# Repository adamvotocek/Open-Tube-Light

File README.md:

# Open-Tube-Light

An open-hardware LED tube fixture for stage and installation lighting. It takes Art-Net over Ethernet or DMX512 over XLR and drives a 144-pixel SK9822 strip inside an acrylic tube, with an OLED status display and buttons on the fixture.

## Repository layout

| Path | Contents |
|---|---|
| [`Code/Open-Tube-Light/`](Code/Open-Tube-Light/) | STM32H723 firmware (CubeMX + FreeRTOS + LwIP) — see its [README](Code/Open-Tube-Light/README.md) |
| [`PCB/ledTubeFixture/`](PCB/ledTubeFixture/) | Main board, KiCad (MCU, Ethernet, DMX, power, display & buttons) |
| [`PCB/xlrConBoards/`](PCB/xlrConBoards/) | XLR connector boards, KiCad |
| [`PCB/releases/`](PCB/releases/) | Fabrication packages for released board revisions |
| [`PCB/TODOs.txt`](PCB/TODOs.txt) | Known issues for the next board revision |
| [`Enclosure/`](Enclosure/) | Mechanical drawings (acrylic tube) |

## Art-Net

The fixture is an Art-Net 4 node (output only). Discovery (ArtPoll), ArtSync, ArtCommand and ArtDataRequest (product, user guide and support URLs) are supported. Spec coverage is tracked in [`Code/Open-Tube-Light/docs/artnet-compliance.md`](Code/Open-Tube-Light/docs/artnet-compliance.md).

**Multiple controllers / merging.** The fixture does not merge (no HTP/LTP). Each universe is owned by the first controller that sends ArtDmx to it. ArtDmx for that universe from any other IP address is ignored until the owner has sent nothing for 5 seconds, after which the next sender takes over. ArtSync is honoured per controller: a universe enters synchronous mode only on ArtSync from its own controller.

Art-Net™ Designed by and Copyright Artistic Licence

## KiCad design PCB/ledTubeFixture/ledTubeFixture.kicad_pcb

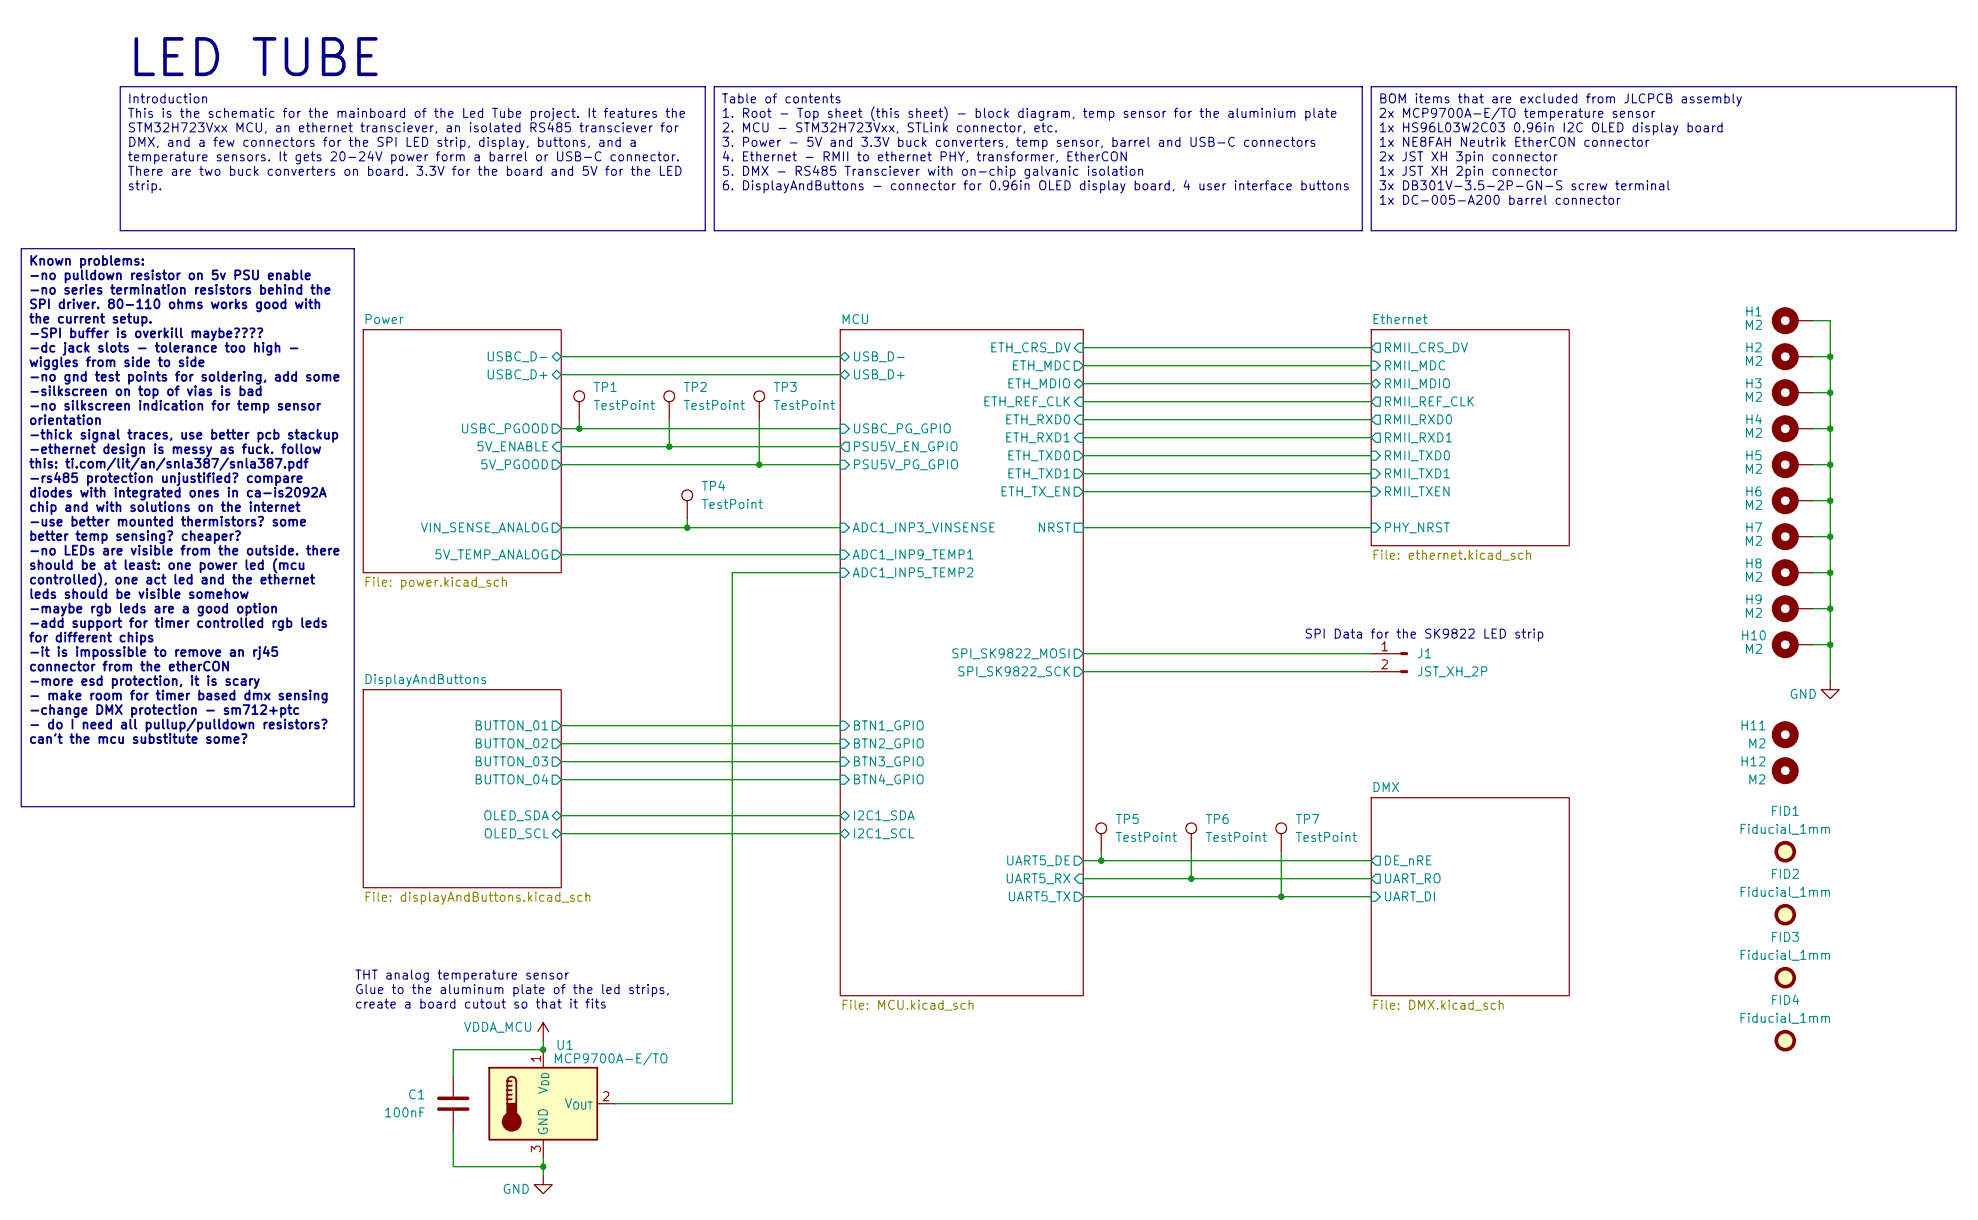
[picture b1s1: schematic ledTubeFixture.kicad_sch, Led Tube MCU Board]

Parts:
C1: 100nF; C_0402_1005Metric; LCSC C1525
FID1, FID2, FID3, FID4: Fiducial_1mm; Fiducial_1mm_Mask2mm
H1, H2, H3, H4, H5, H6, H7, H8, H9, H10: M2; MountingHole_2.2mm_M2_Pad_Via
H11, H12: M2; MountingHole_2.2mm_M2
J1: JST_XH_2P; JST_XH_B2B-XH-A_1x02_P2.50mm_Vertical
TP1, TP2, TP3, TP4, TP5, TP6, TP7: TestPoint; TestPoint_Pad_D1.0mm
U1: MCP9700A-E/TO; TO-92_Inline

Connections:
/DMX/DE_nRE: TP5.1; also elsewhere on the board
/DMX/UART_DI: TP7.1; also elsewhere on the board
/DMX/UART_RO: TP6.1; also elsewhere on the board
/MCU/ADC1_INP3_VINSENSE: TP4.1; also elsewhere on the board
/MCU/ADC1_INP5_TEMP2: U1.2 (V_{OUT}); also elsewhere on the board
/MCU/PSU5V_PG_GPIO: TP3.1; also elsewhere on the board
/MCU/SPI_SK9822_MOSI: J1.1; also elsewhere on the board
/MCU/SPI_SK9822_SCK: J1.2; also elsewhere on the board
/MCU/USBC_PG_GPIO: TP1.1; also elsewhere on the board
/Power/5V_ENABLE: TP2.1; also elsewhere on the board
GND: C1.2, H1.1, H2.1, H3.1, H4.1, H5.1, H6.1, H7.1, H8.1, H9.1, H10.1, U1.3 (GND); also elsewhere on the board
VDDA_MCU: C1.1, U1.1 (V_{DD}); also elsewhere on the board

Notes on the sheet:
THT analog temperature sensor Glue to the aluminum plate of the led strips, create a board cutout so that it fits
LED TUBE
SPI Data for the SK9822 LED strip
Known problems: -no pulldown resistor on 5v PSU enable -no series termination resistors behind the SPI driver. 80-110 ohms works good with the current setup. -SPI buffer is overkill maybe???? -dc jack slots - tolerance too high - wiggles from side to side -no gnd test points for soldering, add some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
Introduction This is the schematic for the mainboard of the Led Tube project. It features the STM32H723Vxx MCU, an ethernet transciever, an isolated RS485 transciever for DMX, and a few connectors for the SPI LED strip, display, buttons, and a temperature sensors. It gets 20-24V power form a barrel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
BOM items that are excluded from JLCPCB assembly 2x MCP9700A-E/TO temperature sensor 1x HS96L03W2C03 0.96in I2C OLED display board 1x NE8FAH Neutrik EtherCON connector 2x JST XH 3pin connector 1x JST XH 2pin connector 3x DB301V-3.5-2P-GN-S screw terminal 1x DC-005-A200 barrel connector
Table of contents 1. Root - Top sheet (this sheet) - block diagram, temp sensor for the aluminium plate 2. MCU - STM32H723Vxx, STLink connector, etc. 3. Power - 5V and 3.3V buck converters, temp sensor, barrel and USB-C connectors 4. Ethernet - RMII to ethernet PHY, transformer, EtherCON 5. DMX - R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

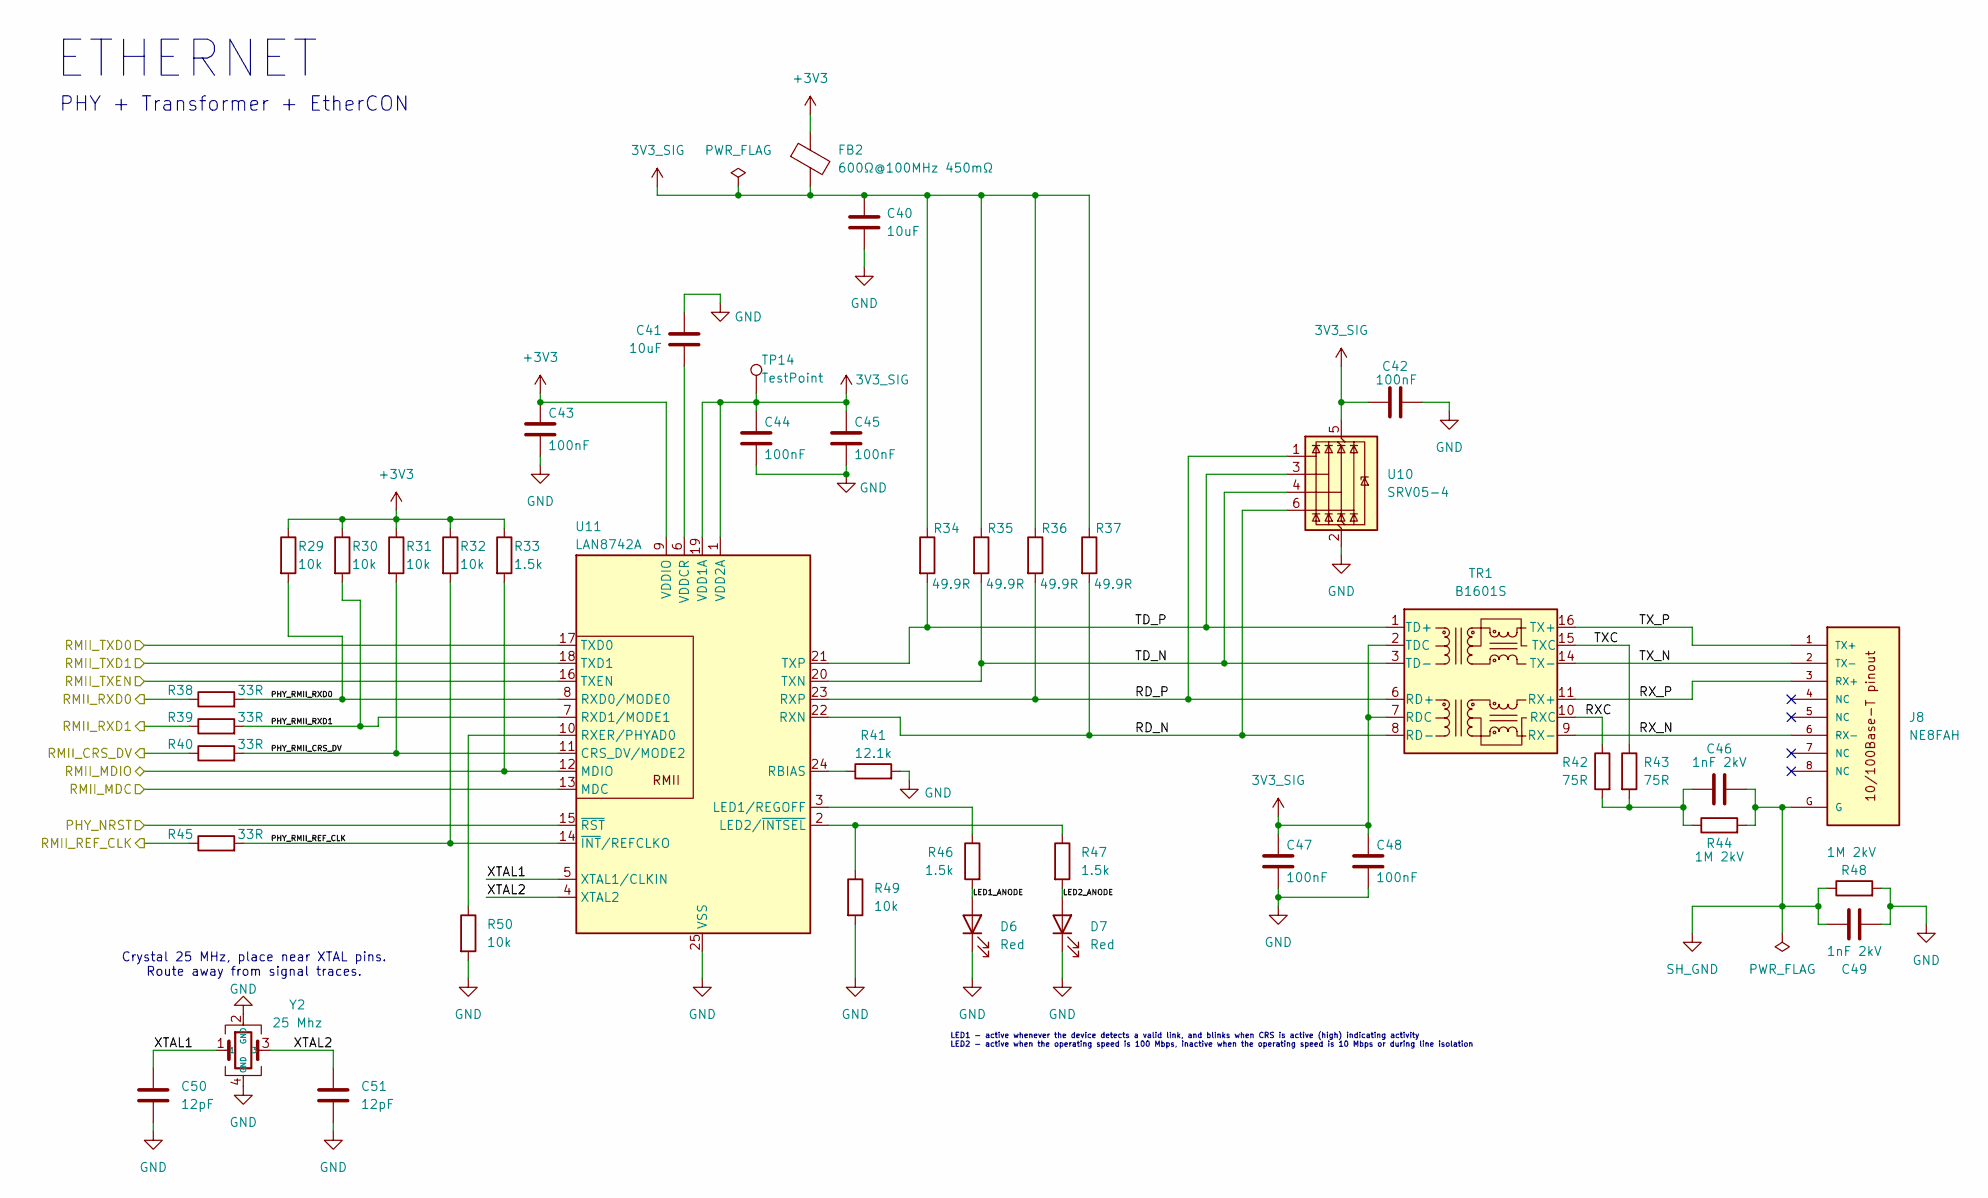
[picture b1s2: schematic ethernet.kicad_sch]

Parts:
C40, C41: 10uF; C_0603_1608Metric; LCSC C19702
C42, C43, C44, C45, C47, C48: 100nF; C_0402_1005Metric; LCSC C1525
C46, C49: 1nF 2kV; C_1206_3216Metric; LCSC C9196
C50, C51: 12pF; C_0402_1005Metric; LCSC C1547
D6, D7: Red; LED_0603_1608Metric; LCSC C2286
FB2: 600Ω@100MHz 450mΩ; C_0603_1608Metric; LCSC C1002
J8: NE8FAH; NEUTRIK_NE8FAH; PARTREV 16.04.02; LCSC C368497
R29, R30, R31, R32, R49, R50: 10k; R_0402_1005Metric; LCSC C25744
R33, R46, R47: 1.5k; R_0402_1005Metric; LCSC C25867
R34, R35, R36, R37: 49.9R; R_0402_1005Metric; LCSC C25120
R38, R39, R40, R45: 33R; R_0402_1005Metric; LCSC C25105
R41: 12.1k; R_0402_1005Metric; LCSC C2933069
R42, R43: 75R; R_0603_1608Metric; LCSC C4275
R44, R48: 1M 2kV; R_2010_5025Metric; LCSC C2779367
TP14: TestPoint; TestPoint_Pad_D1.0mm
TR1: B1601S; Transformer_Ethernet_B1601S; LCSC C510548
U10: SRV05-4; SOT-23-6; LCSC C7420376
U11: LAN8742A; LAN8742A_VQFN-24-1EP_4x4mm_P0.5mm_EP2.5x2.5mm; LCSC C621425
Y2: 25 Mhz; Crystal_SMD_3225-4Pin_3.2x2.5mm; LCSC C9006

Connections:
3V3_SIG: C40.1, C42.1, C44.1, C45.1, C47.1, C48.1, FB2.2, R34.1, R35.1, R36.1, R37.1, TP14.1, TR1.2 (TDC), TR1.7 (RDC), U10.5 (VBUS), U11.1 (VDD2A), U11.19 (VDD1A)
+3V3: C43.1, FB2.1, R29.1, R30.1, R31.1, R32.1, R33.1, U11.9 (VDDIO); also elsewhere on the board
/Ethernet/LED1_ANODE: D6.2 (A), R46.2
/Ethernet/LED2_ANODE: D7.2 (A), R47.2
/Ethernet/PHY_RMII_CRS_DV: R31.2, R40.2, U11.11 (CRS_DV/MODE2)
/Ethernet/PHY_RMII_REF_CLK: R32.2, R45.2, U11.14 (~INT/REFCLKO)
/Ethernet/PHY_RMII_RXD0: R29.2, R38.2, U11.8 (RXD0/MODE0)
/Ethernet/PHY_RMII_RXD1: R30.2, R39.2, U11.7 (RXD1/MODE1)
/Ethernet/RD_N: R37.2, TR1.8 (RD-), U10.6 (I/O4), U11.22 (RXN)
/Ethernet/RD_P: R36.2, TR1.6 (RD+), U10.1 (I/O1), U11.23 (RXP)
/Ethernet/RMII_CRS_DV: R40.1; also elsewhere on the board
/Ethernet/RMII_MDC: U11.13 (MDC); also elsewhere on the board
/Ethernet/RMII_MDIO: R33.2, U11.12 (MDIO); also elsewhere on the board
/Ethernet/RMII_REF_CLK: R45.1; also elsewhere on the board
/Ethernet/RMII_RXD0: R38.1; also elsewhere on the board
/Ethernet/RMII_RXD1: R39.1; also elsewhere on the board
/Ethernet/RMII_TXD0: U11.17 (TXD0); also elsewhere on the board
/Ethernet/RMII_TXD1: U11.18 (TXD1); also elsewhere on the board
/Ethernet/RMII_TXEN: U11.16 (TXEN); also elsewhere on the board
/Ethernet/RXC: R42.1, TR1.10 (RXC)
/Ethernet/RX_N: J8.6 (RX-), TR1.9 (RX-)
/Ethernet/RX_P: J8.3 (RX+), TR1.11 (RX+)
/Ethernet/TD_N: R35.2, TR1.3 (TD-), U10.4 (I/O3), U11.20 (TXN)
/Ethernet/TD_P: R34.2, TR1.1 (TD+), U10.3 (I/O2), U11.21 (TXP)
/Ethernet/TXC: R43.1, TR1.15 (TXC)
/Ethernet/TX_N: J8.2 (TX-), TR1.14 (TX-)
/Ethernet/TX_P: J8.1 (TX+), TR1.16 (TX+)
/Ethernet/XTAL1: C50.1, U11.5 (XTAL1/CLKIN), Y2.1
/Ethernet/XTAL2: C51.1, U11.4 (XTAL2), Y2.3
/MCU/NRST: U11.15 (~RST); also elsewhere on the board
GND: C40.2, C41.1, C42.2, C43.2, C44.2, C45.2, C47.2, C48.2, C49.1, C50.2, C51.2, D6.1 (K), D7.1 (K), R41.2, R48.2, R49.2, R50.2, U10.2 (GND), U11.25 (VSS), Y2.2 (GND), Y2.4 (GND); also elsewhere on the board
unnamed: C46.1, R42.2, R43.2, R44.1
unnamed: R46.1, U11.3 (LED1/REGOFF)
unnamed: R47.1, R49.1, U11.2 (LED2/~INTSEL)
unnamed: R41.1, U11.24 (RBIAS)
unnamed: R50.1, U11.10 (RXER/PHYAD0)
unnamed: C41.2, U11.6 (VDDCR)
SH_GND: C46.2, C49.2, J8.G, R44.2, R48.1

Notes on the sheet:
LED1 - active whenever the device detects a valid link, and blinks when CRS is active (high) indicating activity LED2 - active when the operating speed is 100 Mbps, inactive when the operating speed is 10 Mbps or during line isolation
PHY + Transformer + EtherCON
ETHERNET
Crystal 25 MHz, place near XTAL pins. Route away from signal traces.

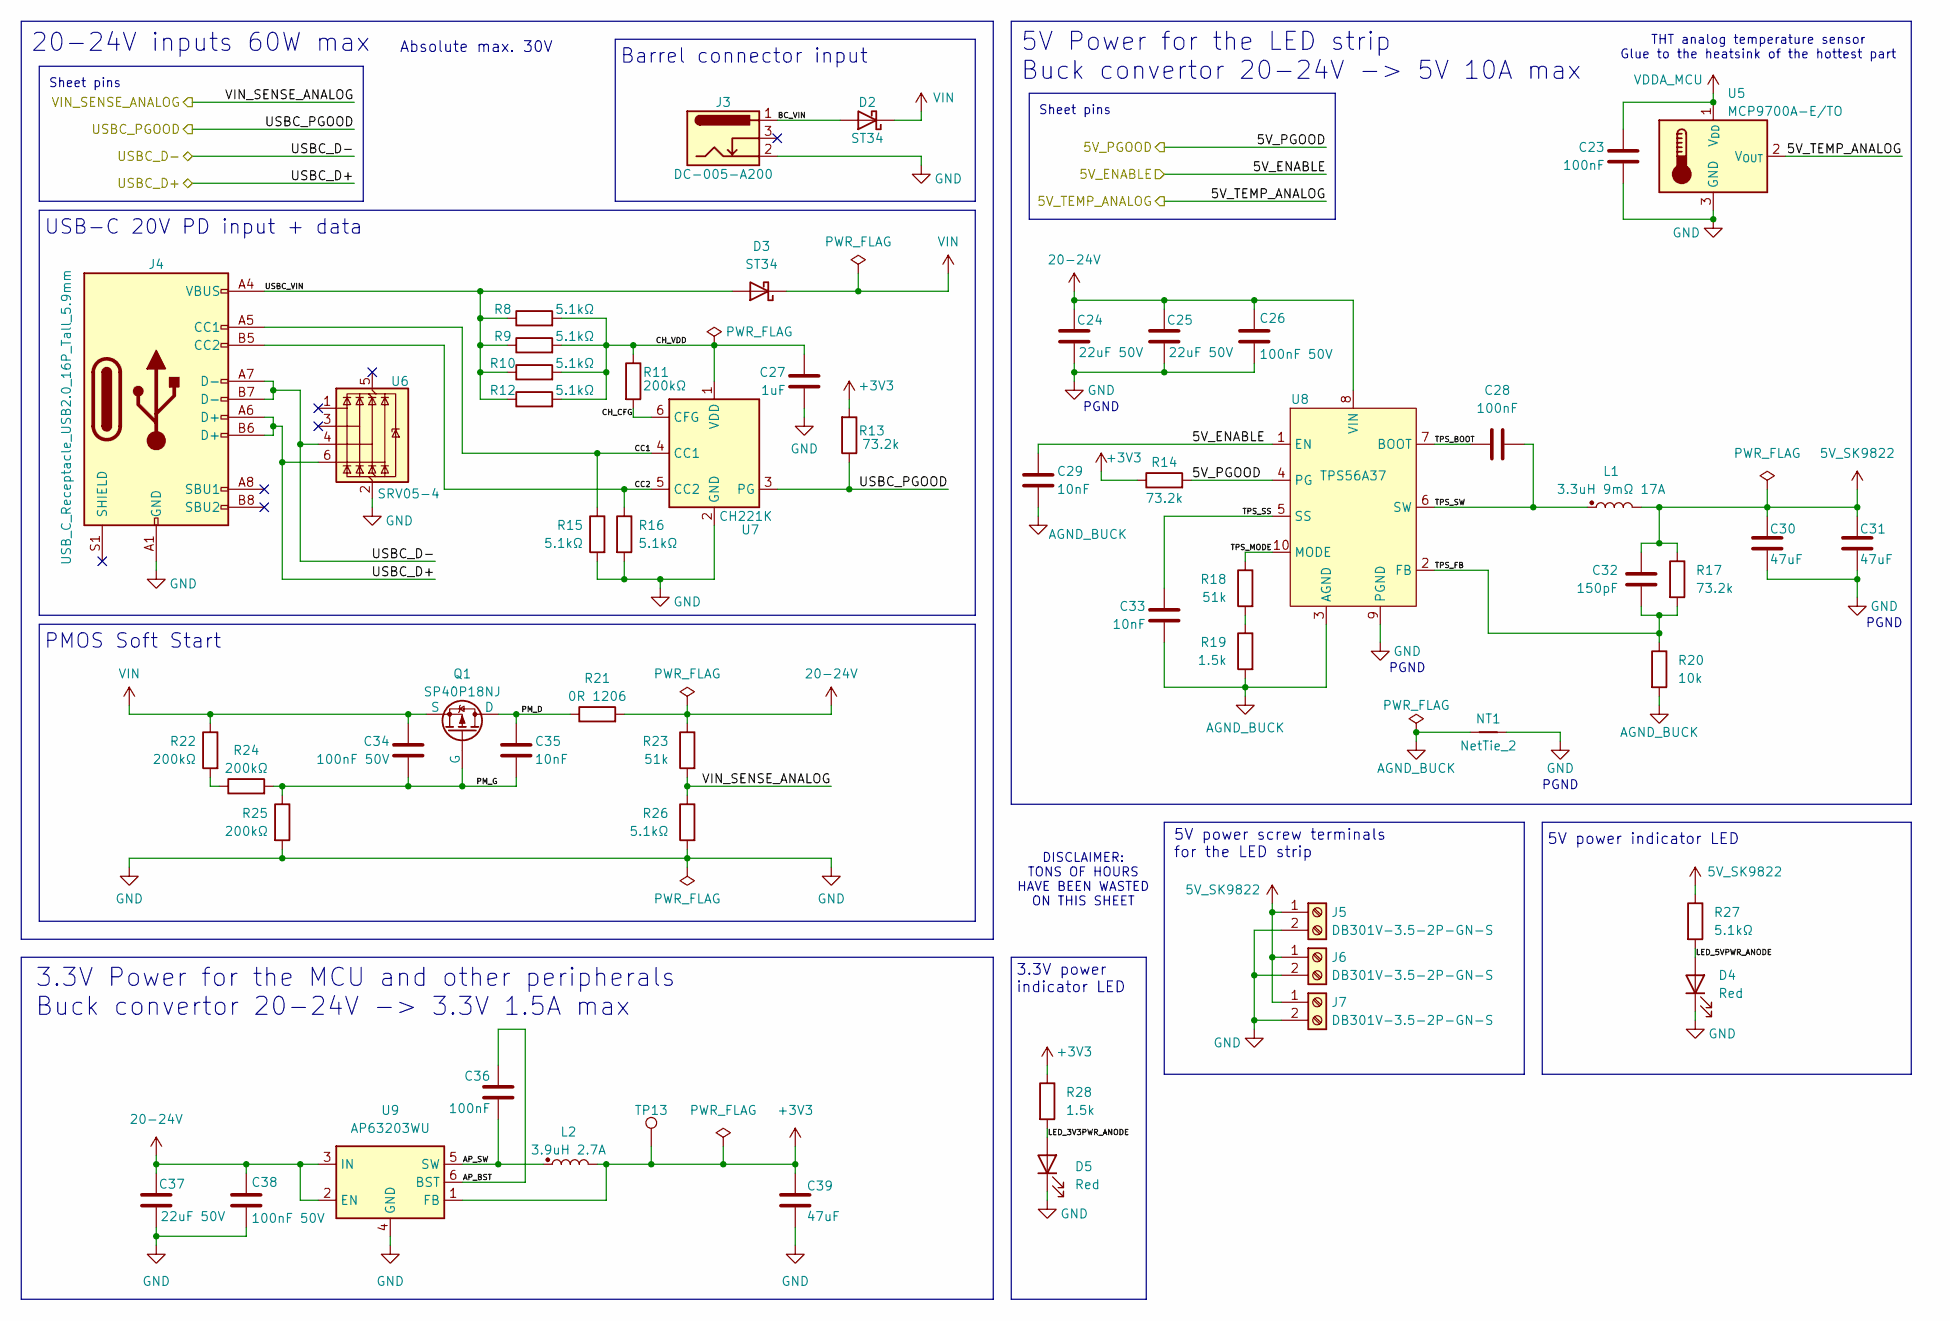
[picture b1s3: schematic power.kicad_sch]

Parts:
C23, C28, C36: 100nF; C_0402_1005Metric; LCSC C1525
C24, C25, C37: 22uF 50V; C_1812_4532Metric; LCSC C22388553
C26, C34, C38: 100nF 50V; C_0402_1005Metric; LCSC C307331
C27: 1uF; C_0402_1005Metric; LCSC C52923
C29, C33, C35: 10nF; C_0402_1005Metric; LCSC C15195
C30, C31, C39: 47uF; C_1210_3225Metric; LCSC C5189825
C32: 150pF; C_0402_1005Metric; LCSC C20069327
D2, D3: ST34; D_SMA; LCSC C413996
D4, D5: Red; LED_0603_1608Metric; LCSC C2286
J3: DC-005-A200; BarrelJack_DC-005-A200_Horizontal; LCSC C720557
J4: USB_C_Receptacle_USB2.0_16P_Tall_5.9mm; USB_C_Receptacle_HX_TYPE-C_16P+4.3; LCSC C32713314
J5, J6, J7: DB301V-3.5-2P-GN-S; TerminalBlock_4Ucon_1x02_P3.50mm_Horizontal; LCSC C695629
L1: 3.3uH 9mΩ 17A; MDA1050-3R3M; LCSC C2847560
L2: 3.9uH 2.7A; L_APV_ANR5020; LCSC C167928
NT1: NetTie_2; NetTie-2_SMD_Pad0.5mm
Q1: SP40P18NJ; PDFN3X3-8L; LCSC C41355197
R8, R9, R10, R12, R15, R16, R26, R27: 5.1kΩ; R_0402_1005Metric; LCSC C25905
R11, R22, R24, R25: 200kΩ; R_0402_1005Metric; LCSC C25764
R13, R14, R17: 73.2k; R_0402_1005Metric; LCSC C26986
R18, R23: 51k; R_0402_1005Metric; LCSC C25794
R19, R28: 1.5k; R_0402_1005Metric; LCSC C25867
R20: 10k; R_0402_1005Metric; LCSC C25744
R21: 0R 1206; R_1206_3216Metric_Pad1.30x1.75mm_HandSolder; LCSC C17888
TP13: TestPoint; TestPoint_Pad_D1.0mm
U5: MCP9700A-E/TO; TO-92_Inline
U6: SRV05-4; SOT-23-6; LCSC C7420376
U7: CH221K; SOT-23-6; LCSC C5125736
U8: TPS56A37; TPS56A37_10-pin_3x3mm_HotRod_QFN; LCSC C22392669
U9: AP63203WU; TSOT-23-6; LCSC C780769

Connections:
5V_SK9822: C30.1, C31.1, C32.1, J5.1, J6.1, J7.1, L1.2, R17.1, R27.1; also elsewhere on the board
20-24V: C24.1, C25.1, C26.1, C37.1, C38.1, R21.2, R23.1, U8.8 (VIN), U9.2 (EN), U9.3 (IN)
+3V3: C39.1, L2.2, R13.2, R14.1, R28.1, TP13.1, U9.1 (FB); also elsewhere on the board
/MCU/ADC1_INP3_VINSENSE: R23.2, R26.1; also elsewhere on the board
/MCU/ADC1_INP9_TEMP1: U5.2 (V_{OUT}); also elsewhere on the board
/MCU/PSU5V_PG_GPIO: R14.2, U8.4 (PG); also elsewhere on the board
/MCU/USBC_PG_GPIO: R13.1, U7.3 (PG); also elsewhere on the board
/Power/5V_ENABLE: C29.1, U8.1 (EN); also elsewhere on the board
/Power/AP_BST: C36.1, U9.6 (BST)
/Power/AP_SW: C36.2, L2.1, U9.5 (SW)
/Power/BC_VIN: D2.2 (A), J3.1
/Power/CC1: J4.A5 (CC1), R15.1, U7.4 (CC1)
/Power/CC2: J4.B5 (CC2), R16.1, U7.5 (CC2)
/Power/CH_CFG: R11.2, U7.6 (CFG)
/Power/CH_VDD: C27.1, R8.2, R9.2, R10.2, R11.1, R12.2, U7.1 (VDD)
/Power/LED_3V3PWR_ANODE: D5.2 (A), R28.2
/Power/LED_5VPWR_ANODE: D4.2 (A), R27.2
/Power/PM_D: C35.1, Q1.3 (D), R21.1
/Power/PM_G: C34.2, C35.2, Q1.2 (G), R24.2, R25.1
/Power/TPS_BOOT: C28.1, U8.7 (BOOT)
/Power/TPS_FB: C32.2, R17.2, R20.1, U8.2 (FB)
/Power/TPS_MODE: R18.1, U8.10 (MODE)
/Power/TPS_SS: C33.1, U8.5 (SS)
/Power/TPS_SW: C28.2, L1.1, U8.6 (SW)
/Power/USBC_D+: J4.A6 (D+), J4.B6 (D+), U6.6 (I/O4); also elsewhere on the board
/Power/USBC_D-: J4.A7 (D-), J4.B7 (D-), U6.4 (I/O3); also elsewhere on the board
/Power/USBC_VIN: D3.2 (A), J4.A4 (VBUS), J4.A9 (VBUS), J4.B4 (VBUS), J4.B9 (VBUS), R8.1, R9.1, R10.1, R12.1
AGND_BUCK: C29.2, C33.2, NT1.1, R19.2, R20.2, U8.3 (AGND)
GND: C23.2, C24.2, C25.2, C26.2, C27.2, C30.2, C31.2, C37.2, C38.2, C39.2, D4.1 (K), D5.1 (K), J3.2, J4.A1 (GND), J4.A12 (GND), J4.B1 (GND), J4.B12 (GND), J5.2, J6.2, J7.2, NT1.2, R15.2, R16.2, R25.2, R26.2, U5.3 (GND), U6.2 (GND), U7.2 (GND), U8.9 (PGND), U9.4 (GND); also elsewhere on the board
unnamed: R18.2, R19.1
unnamed: R22.2, R24.1
VDDA_MCU: C23.1, U5.1 (V_{DD}); also elsewhere on the board
VIN: C34.1, D2.1 (K), D3.1 (K), Q1.1 (S), R22.1

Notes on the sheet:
Absolute max. 30V
3.3V Power for the MCU and other peripherals Buck convertor 20-24V -> 3.3V 1.5A max
PGND
5V power indicator LED
Sheet pins
PMOS Soft Start
3.3V power indicator LED
20-24V inputs 60W max
Barrel connector input
THT analog temperature sensor Glue to the heatsink of the hottest part
5V Power for the LED strip Buck convertor 20-24V -> 5V 10A max
USB-C 20V PD input + data
DISCLAIMER: TONS OF HOURS HAVE BEEN WASTED ON THIS SHEET
5V power screw terminals for the LED strip

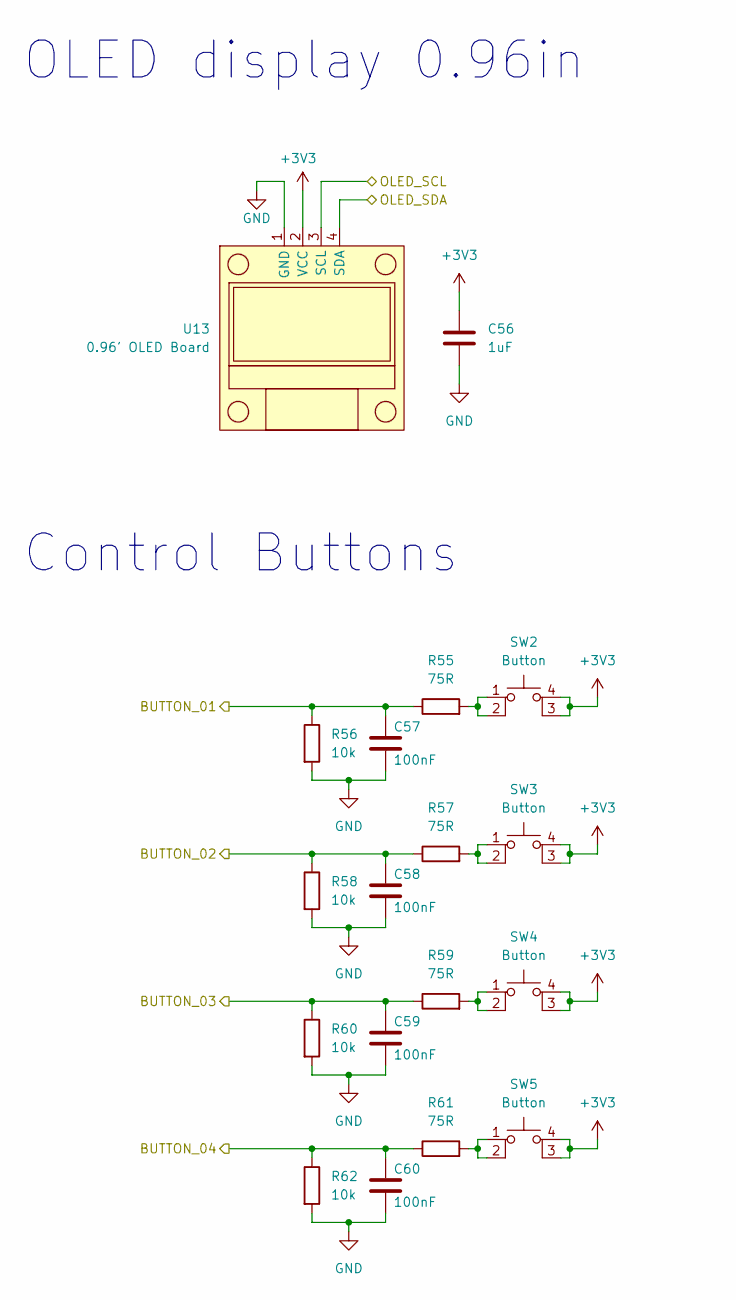
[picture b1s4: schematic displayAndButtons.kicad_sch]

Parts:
C56: 1uF; C_0402_1005Metric; LCSC C52923
C57, C58, C59, C60: 100nF; C_0402_1005Metric; LCSC C1525
R55, R57, R59, R61: 75R; R_0603_1608Metric; LCSC C4275
R56, R58, R60, R62: 10k; R_0402_1005Metric; LCSC C25744
SW2, SW3, SW4, SW5: Button; SW_SPST_4P_SMD; LCSC C455114
U13: 0.96' OLED Board; HS96L03W2C03

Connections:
+3V3: C56.1, SW2.3 (K), SW2.4 (A), SW3.3 (K), SW3.4 (A), SW4.3 (K), SW4.4 (A), SW5.3 (K), SW5.4 (A), U13.2 (VCC); also elsewhere on the board
/DisplayAndButtons/BUTTON_01: C57.1, R55.1, R56.1; also elsewhere on the board
/DisplayAndButtons/BUTTON_02: C58.1, R57.1, R58.1; also elsewhere on the board
/DisplayAndButtons/BUTTON_03: C59.1, R59.1, R60.1; also elsewhere on the board
/DisplayAndButtons/BUTTON_04: C60.1, R61.1, R62.1; also elsewhere on the board
/DisplayAndButtons/OLED_SCL: U13.3 (SCL); also elsewhere on the board
/DisplayAndButtons/OLED_SDA: U13.4 (SDA); also elsewhere on the board
GND: C56.2, C57.2, C58.2, C59.2, C60.2, R56.2, R58.2, R60.2, R62.2, U13.1 (GND); also elsewhere on the board
unnamed: R55.2, SW2.1, SW2.2
unnamed: R57.2, SW3.1, SW3.2
unnamed: R59.2, SW4.1, SW4.2
unnamed: R61.2, SW5.1, SW5.2

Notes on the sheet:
OLED display 0.96in
Control Buttons

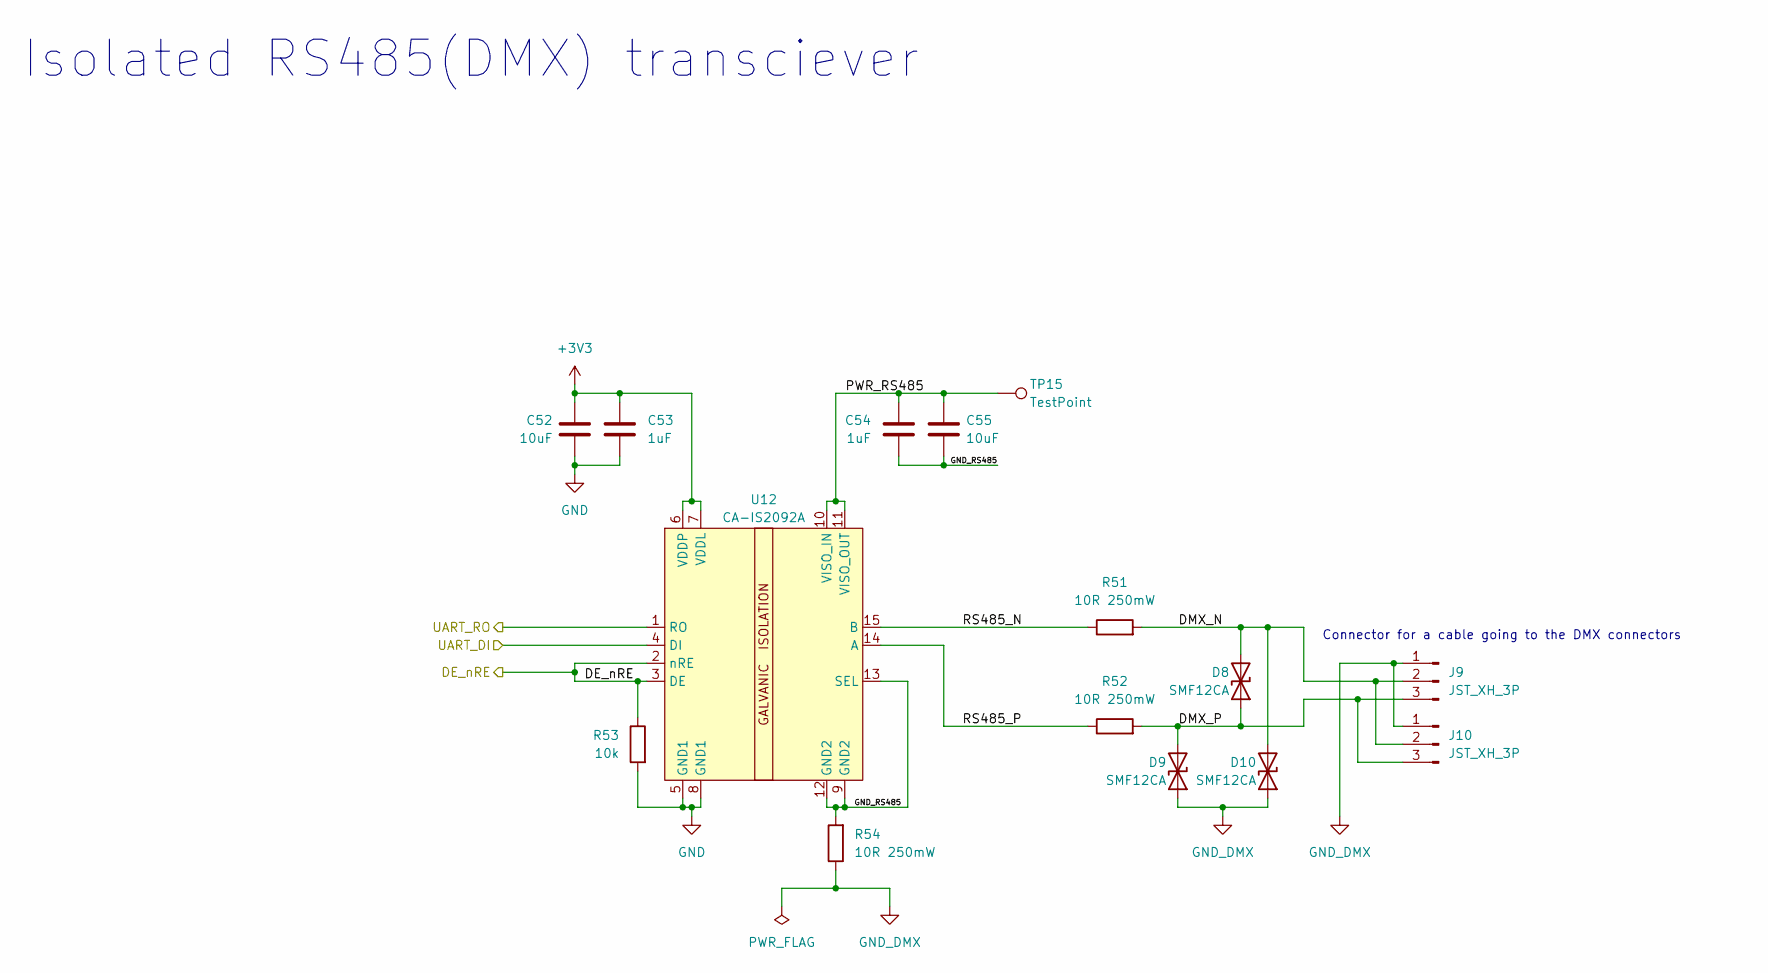
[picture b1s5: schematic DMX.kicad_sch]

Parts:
C52, C55: 10uF; C_0603_1608Metric; LCSC C19702
C53, C54: 1uF; C_0402_1005Metric; LCSC C52923
D8, D9, D10: SMF12CA; D_SOD-123F; LCSC C19077507
J9, J10: JST_XH_3P; JST_XH_B3B-XH-A_1x03_P2.50mm_Vertical
R51, R52, R54: 10R 250mW; R_1206_3216Metric; LCSC C17903
R53: 10k; R_0402_1005Metric; LCSC C25744
TP15: TestPoint; TestPoint_Pad_D1.0mm
U12: CA-IS2092A; LCSC C18185406

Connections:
+3V3: C52.1, C53.1, U12.6 (VDDP), U12.7 (VDDL); also elsewhere on the board
/DMX/DE_nRE: R53.1, U12.2 (nRE), U12.3 (DE); also elsewhere on the board
/DMX/DMX_N: D8.2 (A2), D10.2 (A2), J9.2, J10.2, R51.2
/DMX/DMX_P: D8.1 (A1), D9.2 (A2), J9.3, J10.3, R52.2
/DMX/GND_RS485: C54.2, C55.2, R54.2, U12.9 (GND2), U12.12 (GND2), U12.13 (SEL)
/DMX/PWR_RS485: C54.1, C55.1, TP15.1, U12.10 (VISO_IN), U12.11 (VISO_OUT)
/DMX/RS485_N: R51.1, U12.15 (B)
/DMX/RS485_P: R52.1, U12.14 (A)
/DMX/UART_DI: U12.4 (DI); also elsewhere on the board
/DMX/UART_RO: U12.1 (RO); also elsewhere on the board
GND: C52.2, C53.2, R53.2, U12.5 (GND1), U12.8 (GND1); also elsewhere on the board
GND_DMX: D9.1 (A1), D10.1 (A1), J9.1, J10.1, R54.1

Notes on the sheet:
Connector for a cable going to the DMX connectors
Isolated RS485(DMX) transciever

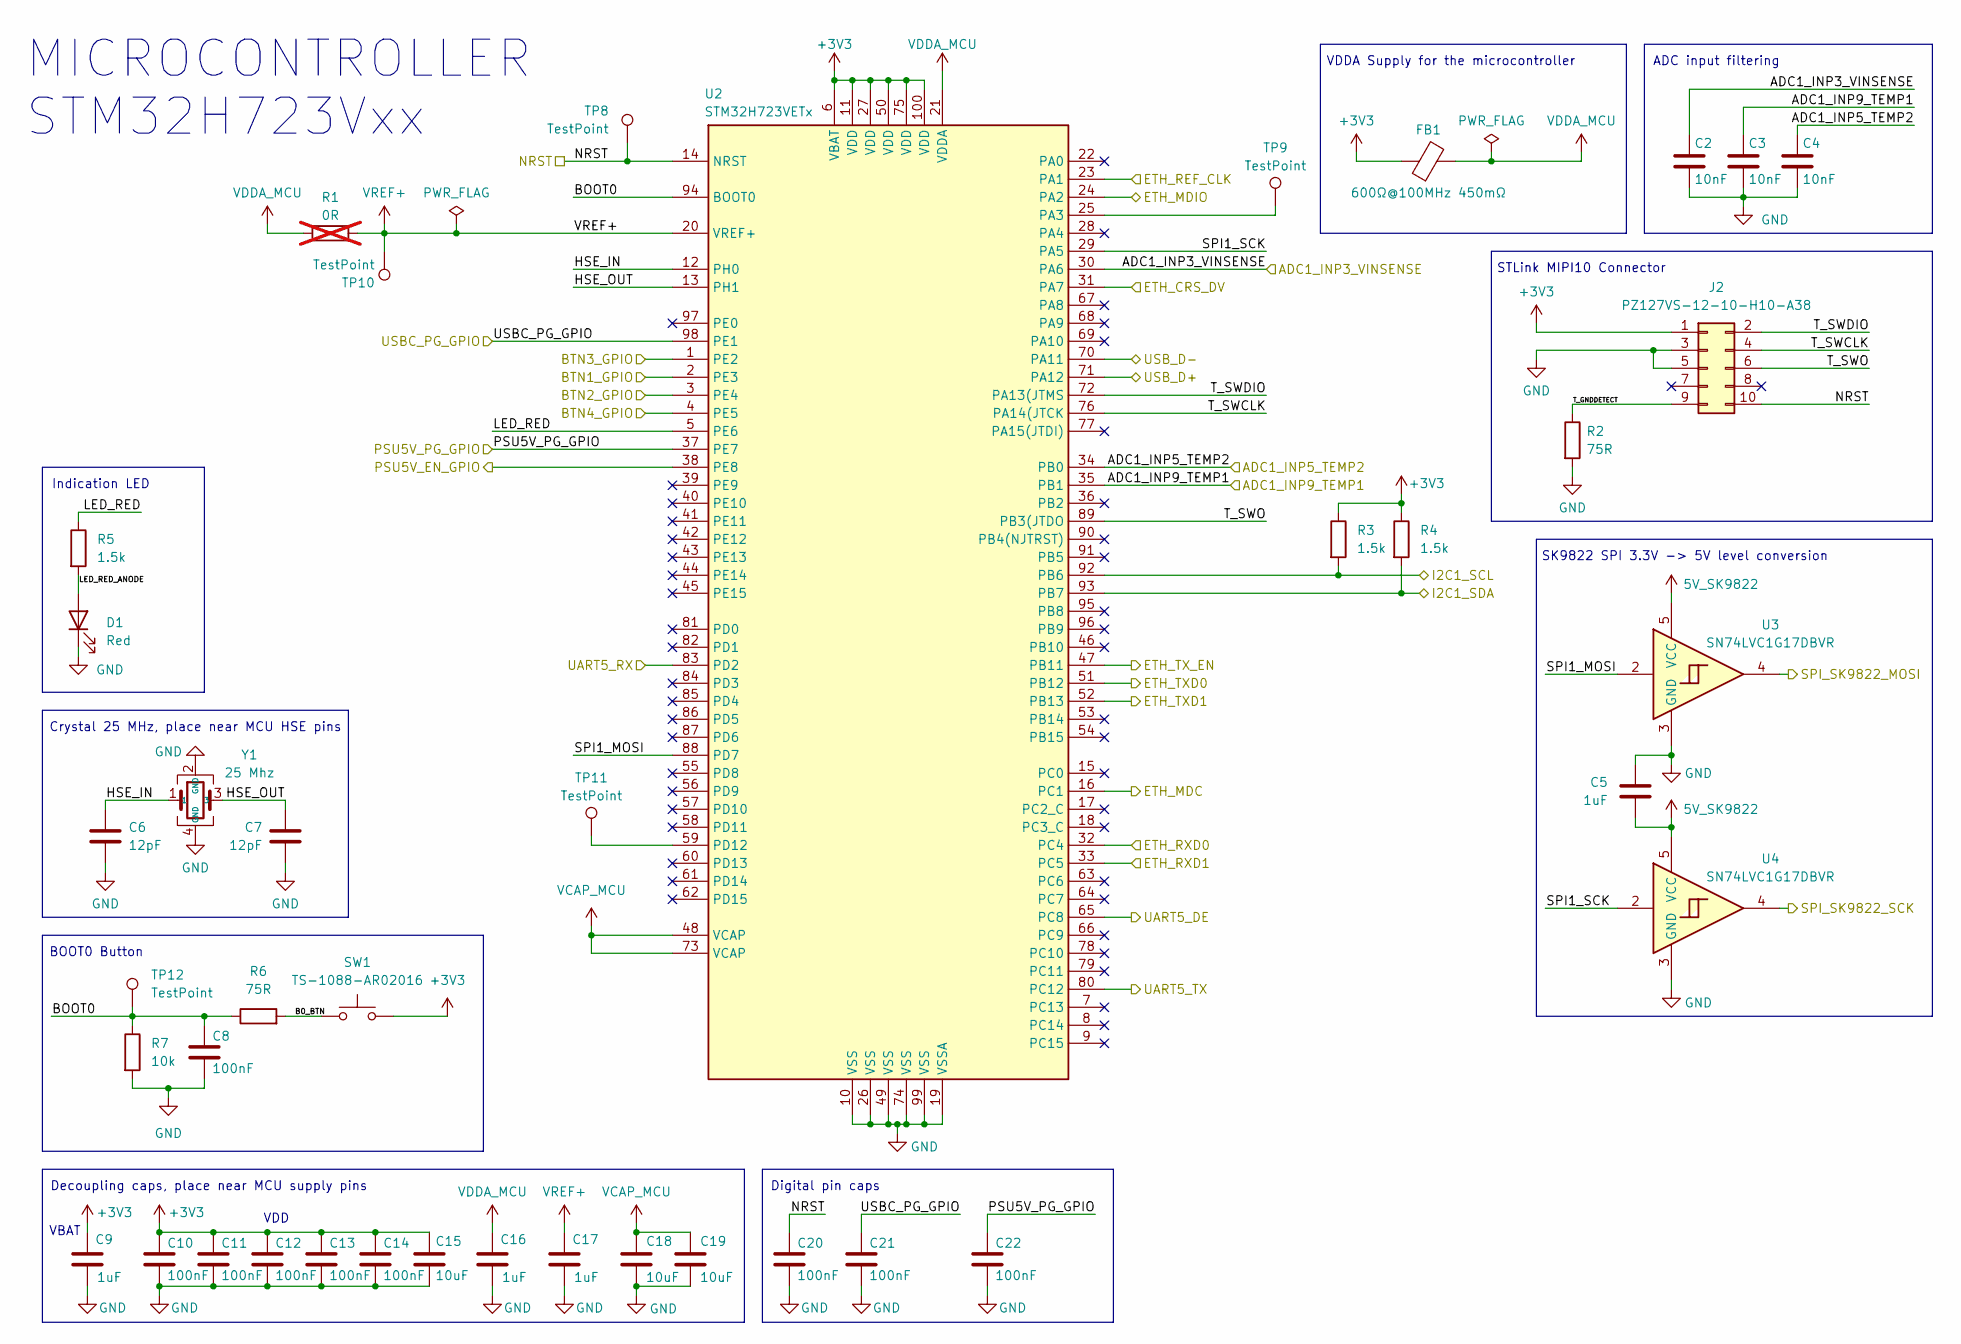
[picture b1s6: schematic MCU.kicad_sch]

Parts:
C2, C3, C4: 10nF; C_0402_1005Metric; LCSC C15195
C5, C9, C16, C17: 1uF; C_0402_1005Metric; LCSC C52923
C6, C7: 12pF; C_0402_1005Metric; LCSC C1547
C8, C10, C11, C12, C13, C14, C20, C21, C22: 100nF; C_0402_1005Metric; LCSC C1525
C15, C18, C19: 10uF; C_0603_1608Metric; LCSC C19702
D1: Red; LED_0603_1608Metric; LCSC C2286
FB1: 600Ω@100MHz 450mΩ; C_0603_1608Metric; LCSC C1002
J2: PZ127VS-12-10-H10-A38; LCSC C2935458
R1: 0R; R_0603_1608Metric_Pad0.98x0.95mm_HandSolder; LCSC C21189; not fitted
R2, R6: 75R; R_0603_1608Metric; LCSC C4275
R3, R4, R5: 1.5k; R_0402_1005Metric; LCSC C25867
R7: 10k; R_0402_1005Metric; LCSC C25744
SW1: TS-1088-AR02016; SW_Push_SPST_NO_Alps_SKRK; LCSC C720477
TP8, TP9, TP10, TP11, TP12: TestPoint; TestPoint_Pad_D1.0mm
U2: STM32H723VETx; LQFP-100_14x14mm_P0.5mm; LCSC C730141
U3, U4: SN74LVC1G17DBVR; SOT-23-5; LCSC C7836
Y1: 25 Mhz; Crystal_SMD_3225-4Pin_3.2x2.5mm; LCSC C9006

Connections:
5V_SK9822: C5.2, U3.5 (VCC), U4.5 (VCC); also elsewhere on the board
+3V3: C9.1, C10.1, C11.1, C12.1, C13.1, C14.1, C15.1, FB1.1, J2.1, R3.1, R4.1, SW1.2, U2.6 (VBAT), U2.11 (VDD), U2.27 (VDD), U2.50 (VDD), U2.75 (VDD), U2.100 (VDD); also elsewhere on the board
/DMX/DE_nRE: U2.65 (PC8); also elsewhere on the board
/DMX/UART_DI: U2.80 (PC12); also elsewhere on the board
/DMX/UART_RO: U2.83 (PD2); also elsewhere on the board
/DisplayAndButtons/BUTTON_01: U2.2 (PE3); also elsewhere on the board
/DisplayAndButtons/BUTTON_02: U2.3 (PE4); also elsewhere on the board
/DisplayAndButtons/BUTTON_03: U2.1 (PE2); also elsewhere on the board
/DisplayAndButtons/BUTTON_04: U2.4 (PE5); also elsewhere on the board
/DisplayAndButtons/OLED_SCL: R3.2, U2.92 (PB6); also elsewhere on the board
/DisplayAndButtons/OLED_SDA: R4.2, U2.93 (PB7); also elsewhere on the board
/Ethernet/RMII_CRS_DV: U2.31 (PA7); also elsewhere on the board
/Ethernet/RMII_MDC: U2.16 (PC1); also elsewhere on the board
/Ethernet/RMII_MDIO: U2.24 (PA2); also elsewhere on the board
/Ethernet/RMII_REF_CLK: U2.23 (PA1); also elsewhere on the board
/Ethernet/RMII_RXD0: U2.32 (PC4); also elsewhere on the board
/Ethernet/RMII_RXD1: U2.33 (PC5); also elsewhere on the board
/Ethernet/RMII_TXD0: U2.51 (PB12); also elsewhere on the board
/Ethernet/RMII_TXD1: U2.52 (PB13); also elsewhere on the board
/Ethernet/RMII_TXEN: U2.47 (PB11); also elsewhere on the board
/MCU/ADC1_INP3_VINSENSE: C2.1, U2.30 (PA6); also elsewhere on the board
/MCU/ADC1_INP5_TEMP2: C4.1, U2.34 (PB0); also elsewhere on the board
/MCU/ADC1_INP9_TEMP1: C3.1, U2.35 (PB1); also elsewhere on the board
/MCU/B0_BTN: R6.2, SW1.1
/MCU/BOOT0: C8.1, R6.1, R7.1, TP12.1, U2.94 (BOOT0)
/MCU/HSE_IN: C6.1, U2.12 (PH0), Y1.1
/MCU/HSE_OUT: C7.1, U2.13 (PH1), Y1.3
/MCU/LED_RED: R5.1, U2.5 (PE6)
/MCU/LED_RED_ANODE: D1.2 (A), R5.2
/MCU/NRST: C20.1, J2.10, TP8.1, U2.14 (NRST); also elsewhere on the board
/MCU/PSU5V_PG_GPIO: C22.1, U2.37 (PE7); also elsewhere on the board
/MCU/SPI1_MOSI: U2.88 (PD7), U3.2
/MCU/SPI1_SCK: U2.29 (PA5), U4.2
/MCU/SPI_SK9822_MOSI: U3.4; also elsewhere on the board
/MCU/SPI_SK9822_SCK: U4.4; also elsewhere on the board
/MCU/T_GNDDETECT: J2.9, R2.1
/MCU/T_SWCLK: J2.4, U2.76 (PA14(JTCK)
/MCU/T_SWDIO: J2.2, U2.72 (PA13(JTMS)
/MCU/T_SWO: J2.6, U2.89 (PB3(JTDO)
/MCU/USBC_PG_GPIO: C21.1, U2.98 (PE1); also elsewhere on the board
/Power/5V_ENABLE: U2.38 (PE8); also elsewhere on the board
/Power/USBC_D+: U2.71 (PA12); also elsewhere on the board
/Power/USBC_D-: U2.70 (PA11); also elsewhere on the board
GND: C2.2, C3.2, C4.2, C5.1, C6.2, C7.2, C8.2, C9.2, C10.2, C11.2, C12.2, C13.2, C14.2, C15.2, C16.2, C17.2, C18.2, C19.2, C20.2, C21.2, C22.2, D1.1 (K), J2.3, J2.5, R2.2, R7.2, U2.10 (VSS), U2.19 (VSSA), U2.26 (VSS), U2.49 (VSS), U2.74 (VSS), U2.99 (VSS), U3.3 (GND), U4.3 (GND), Y1.2 (GND), Y1.4 (GND); also elsewhere on the board
unnamed: TP9.1, U2.25 (PA3)
unnamed: TP11.1, U2.59 (PD12)
VCAP_MCU: C18.1, C19.1, U2.48 (VCAP), U2.73 (VCAP)
VDDA_MCU: C16.1, FB1.2, R1.1, U2.21 (VDDA); also elsewhere on the board
VREF+: C17.1, R1.2, TP10.1, U2.20 (VREF+)

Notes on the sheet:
Decoupling caps, place near MCU supply pins
VDD
MICROCONTROLLER STM32H723Vxx
ADC input filtering
SK9822 SPI 3.3V -> 5V level conversion
VBAT
STLink MIPI10 Connector
BOOT0 Button
Crystal 25 MHz, place near MCU HSE pins
Digital pin caps
Indication LED
VDDA Supply for the microcontroller
